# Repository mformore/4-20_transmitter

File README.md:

# 4-20mA and 0-10V Arduino Shield Transmitter

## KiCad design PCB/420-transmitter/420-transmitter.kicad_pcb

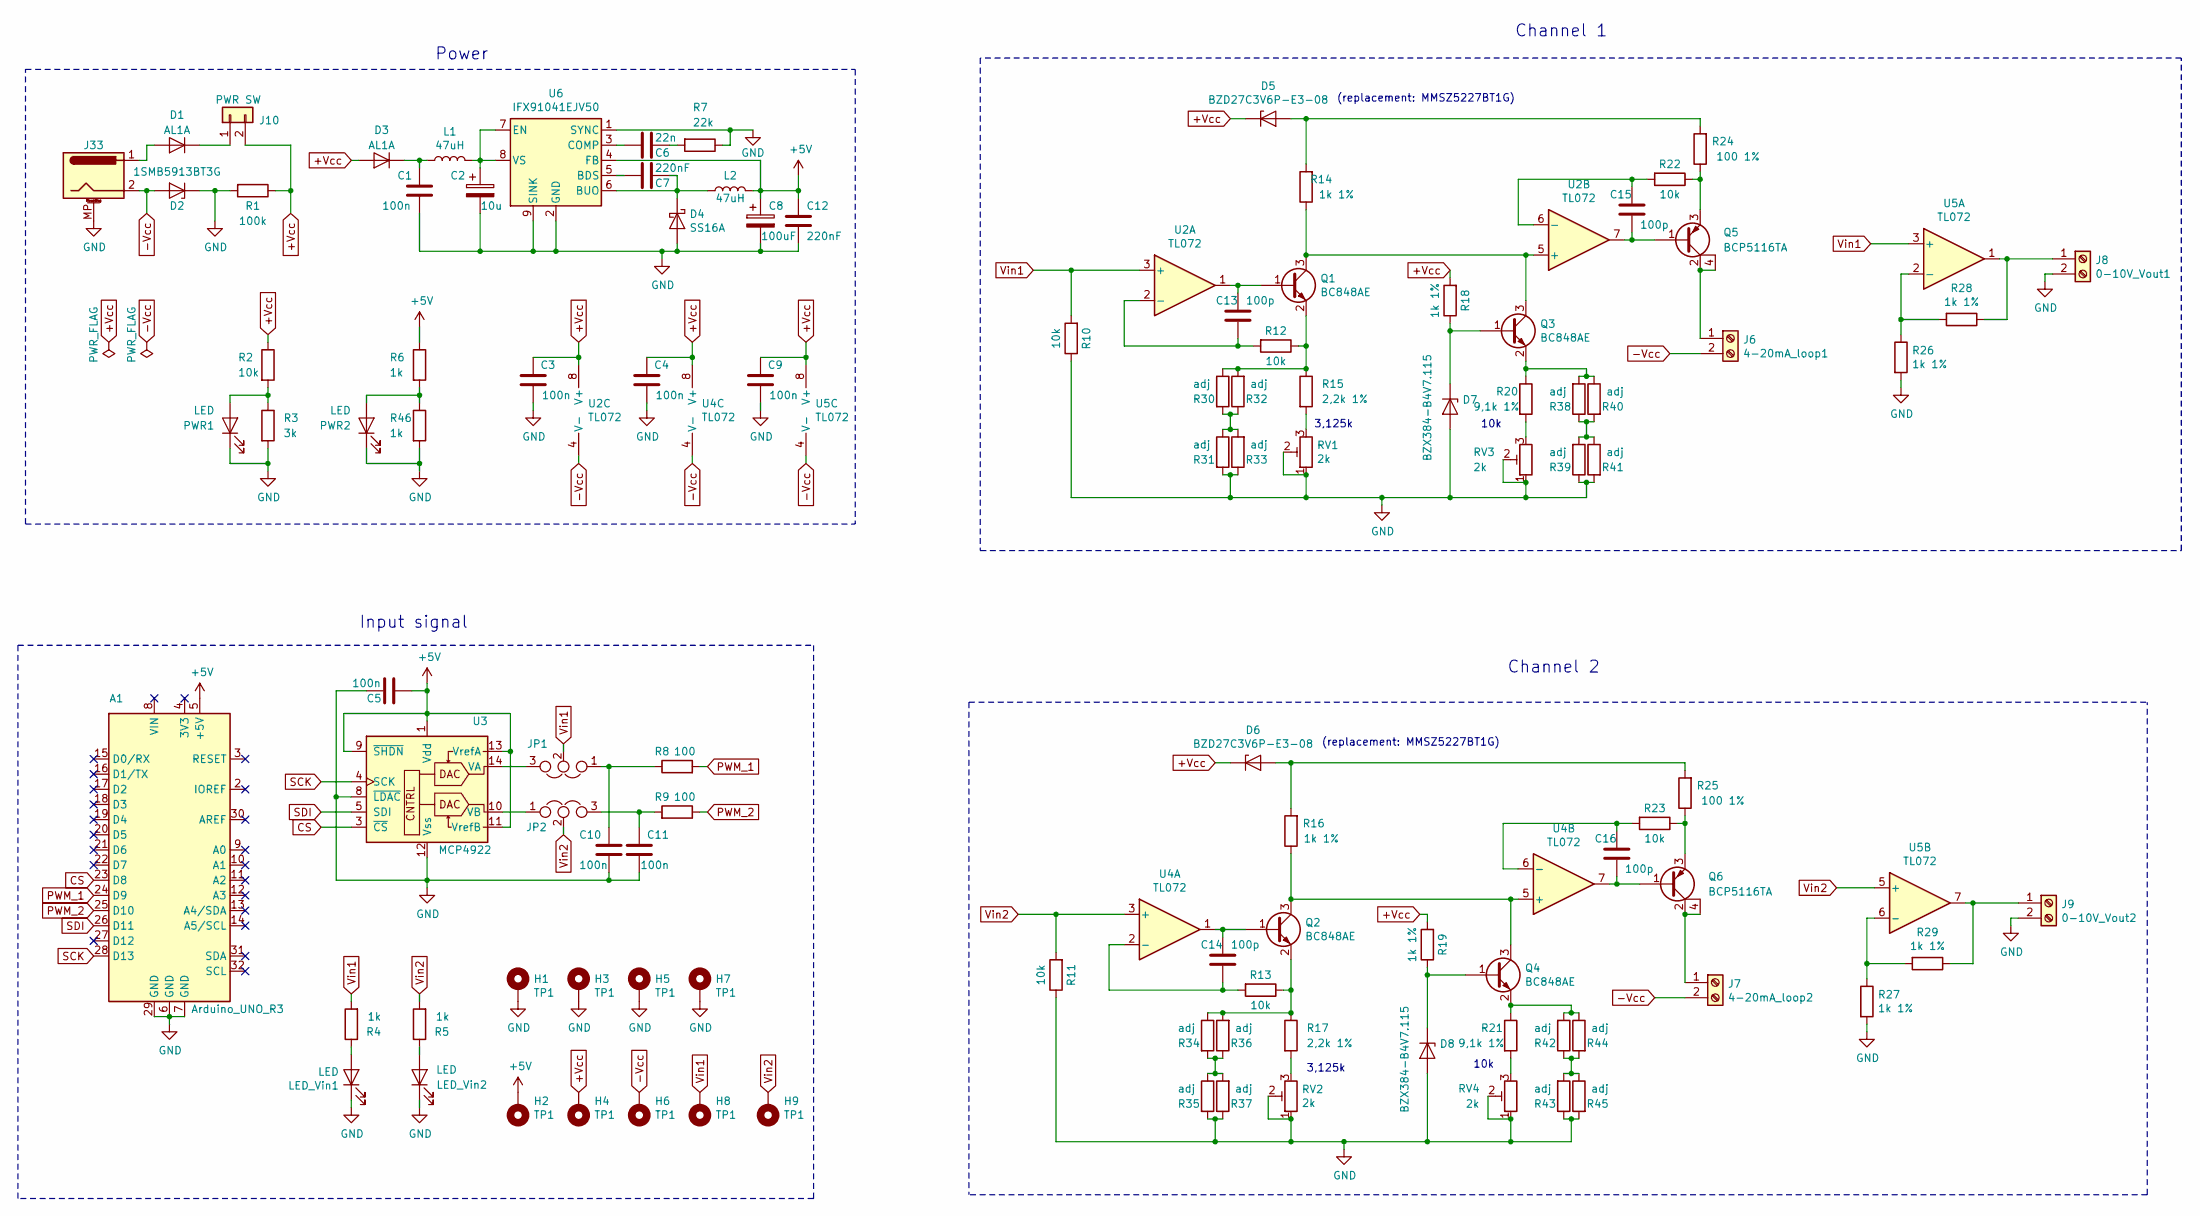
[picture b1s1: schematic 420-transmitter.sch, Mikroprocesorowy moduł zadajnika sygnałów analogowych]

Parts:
A1: Arduino_UNO_R3
C1, C3, C4, C5, C9, C10, C11: 100n; C_0805_2012Metric
C2: 10u; CP_Elec_6.3x5.3
C6: 22n; C_0805_2012Metric
C7, C12: 220nF; C_0805_2012Metric
C8: 100uF; CP_Elec_6.3x5.3
C13, C14, C15, C16: 100p; C_0805_2012Metric
D1, D3: AL1A; D_MiniMELF
D2: 1SMB5913BT3G; D_SMB
D4: SS16A; D_SMA
D5, D6: BZD27C3V6P-E3-08; D_SOD-123
D7, D8: BZX384-B4V7.115; D_SOD-323
H1, H2, H3, H4, H5, H6, H7, H8, H9: TP1; TestPoint_THTPad_D1.0mm_Drill0.5mm
J6: 4-20mA_loop1; TerminalBlock_bornier-2_P5.08mm
J7: 4-20mA_loop2; TerminalBlock_bornier-2_P5.08mm
J8: 0-10V_Vout1; TerminalBlock_bornier-2_P5.08mm
J9: 0-10V_Vout2; TerminalBlock_bornier-2_P5.08mm
J10: PWR SW; PinHeader_1x02_P2.54mm_Vertical
J33: Barrel_Jack_MountingPin; BarrelJack_Wuerth_6941xx301002
JP1: Vin1; PinHeader_1x03_P2.54mm_Vertical
JP2: Vin2; PinHeader_1x03_P2.54mm_Vertical
L1, L2: 47uH; L_Taiyo-Yuden_MD-5050
LED_Vin1, LED_Vin2: LED; LED_0805_2012Metric
PWR1, PWR2: LED; LED_0805_2012Metric
Q1, Q2, Q3, Q4: BC848AE; SOT-23
Q5, Q6: BCP5116TA; SOT-223
R1: 100k; R_1206_3216Metric
R2, R10, R11, R12, R13, R22, R23: 10k; R_0805_2012Metric
R3: 3k; R_0805_2012Metric
R4, R5, R6, R46: 1k; R_0805_2012Metric
R7: 22k; R_0805_2012Metric
R8, R9: 100; R_0805_2012Metric
R14, R16, R18, R19, R26, R27, R28, R29: 1k 1%; R_0805_2012Metric
R15, R17: 2,2k 1%; R_0805_2012Metric
R20, R21: 9,1k 1%; R_0805_2012Metric
R24, R25: 100 1%; R_2010_5025Metric
R30, R31, R32, R33, R34, R35, R36, R37, R38, R39, R40, R41, R42, R43, R44, R45: adj; R_0805_2012Metric
RV1, RV2, RV3, RV4: 2k; Potentiometer_Bourns_3296W_Vertical
U2, U4, U5: TL072; SO-8_5.3x6.2mm_P1.27mm
U3: MCP4922; SO14
U6: IFX91041EJV50; Infineon_PG-DSO-8-43

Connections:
+5V: A1.5 (+5V), C5.1, C8.1, C12.2, H2.1, L2.2, R6.1, U3.1 (Vdd), U3.9 (~SHDN), U3.11 (VrefB), U3.13 (VrefA), U6.4 (FB)
+Vcc: C3.1, C4.1, C9.1, D3.2 (A), D5.1 (K), D6.1 (K), H4.1, J10.2, R1.1, R2.1, R18.2, R19.2, U2.8 (V+), U4.8 (V+), U5.8 (V+)
-Vcc: D2.2 (A), H6.1, J6.2, J7.2, J33.2, U2.4 (V-), U4.4 (V-), U5.4 (V-)
CS: A1.23 (D8), U3.3 (~CS)
GND: A1.6 (GND), A1.7 (GND), A1.29 (GND), C1.2, C2.2, C3.2, C4.2, C5.2, C8.2, C9.2, C10.1, C11.1, C12.1, D2.1 (K), D4.2 (A), D7.2 (A), D8.2 (A), H1.1, H3.1, H5.1, H7.1, J8.2, J9.2, J33.MP (MountPin), LED_Vin1.1 (K), LED_Vin2.1 (K), PWR1.1 (K), PWR2.1 (K), R1.2, R3.2, R7.1, R10.1, R11.1, R26.2, R27.2, R31.2, R33.1, R35.2, R37.1, R39.1, R41.2, R43.1, R45.2, R46.2, RV1.1, RV1.2, RV2.1, RV2.2, RV3.1, RV3.2, RV4.1, RV4.2, U3.8 (~LDAC), U3.12 (Vss), U6.1 (SYNC), U6.2 (GND), U6.9 (SINK)
unnamed: C1.1, D3.1 (K), L1.1
unnamed: C2.1, L1.2, U6.7 (EN), U6.8 (VS)
unnamed: C6.1, R7.2
unnamed: C6.2, U6.3 (COMP)
unnamed: C7.1, U6.5 (BDS)
unnamed: C7.2, D4.1 (K), L2.1, U6.6 (BUO)
unnamed: C10.2, JP1.1, R8.1
unnamed: C11.2, JP2.3, R9.2
unnamed: C13.1, Q1.1 (B), U2.1
unnamed: C13.2, R12.2, U2.2 (-)
unnamed: C14.1, Q2.1 (B), U4.1
unnamed: C14.2, R13.2, U4.2 (-)
unnamed: C15.1, R22.2, U2.6 (-)
unnamed: C15.2, Q5.1 (B), U2.7
unnamed: C16.1, R23.2, U4.6 (-)
unnamed: C16.2, Q6.1 (B), U4.7
unnamed: D1.1 (K), J10.1
unnamed: D1.2 (A), J33.1
unnamed: D5.2 (A), R14.2, R24.2
unnamed: D6.2 (A), R16.2, R25.2
unnamed: D7.1 (K), Q3.1 (B), R18.1
unnamed: D8.1 (K), Q4.1 (B), R19.1
unnamed: J6.1, Q5.2 (C), Q5.4 (C)
unnamed: J7.1, Q6.2 (C), Q6.4 (C)
unnamed: J8.1, R28.1, U5.1
unnamed: J9.1, R29.1, U5.7
unnamed: JP1.3, U3.14 (VA)
unnamed: JP2.1, U3.10 (VB)
unnamed: LED_Vin1.2 (A), R4.1
unnamed: LED_Vin2.2 (A), R5.1
unnamed: PWR1.2 (A), R2.2, R3.1
unnamed: PWR2.2 (A), R6.2, R46.1
unnamed: Q1.2 (E), R12.1, R15.1, R30.1, R32.2
unnamed: Q1.3 (C), Q3.3 (C), R14.1, U2.5 (+)
unnamed: Q2.2 (E), R13.1, R17.1, R34.1, R36.2
unnamed: Q2.3 (C), Q4.3 (C), R16.1, U4.5 (+)
unnamed: Q3.2 (E), R20.1, R38.2, R40.1
unnamed: Q4.2 (E), R21.1, R42.2, R44.1
unnamed: Q5.3 (E), R22.1, R24.1
unnamed: Q6.3 (E), R23.1, R25.1
unnamed: R15.2, RV1.3
unnamed: R17.2, RV2.3
unnamed: R20.2, RV3.3
unnamed: R21.2, RV4.3
unnamed: R26.1, R28.2, U5.2 (-)
unnamed: R27.1, R29.2, U5.6 (-)
unnamed: R30.2, R31.1, R32.1, R33.2
unnamed: R34.2, R35.1, R36.1, R37.2
unnamed: R38.1, R39.2, R40.2, R41.1
unnamed: R42.1, R43.2, R44.2, R45.1
PWM_1: A1.24 (D9), R8.2
PWM_2: A1.25 (D10), R9.1
SCK: A1.28 (D13), U3.4 (SCK)
SDI: A1.26 (D11), U3.5 (SDI)
Vin1: H8.1, JP1.2, R4.2, R10.2, U2.3 (+), U5.3 (+)
Vin2: H9.1, JP2.2, R5.2, R11.2, U4.3 (+), U5.5 (+)

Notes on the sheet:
Power
Input signal
Channel 1
Channel 2
10k
3,125k
(replacement: MMSZ5227BT1G)

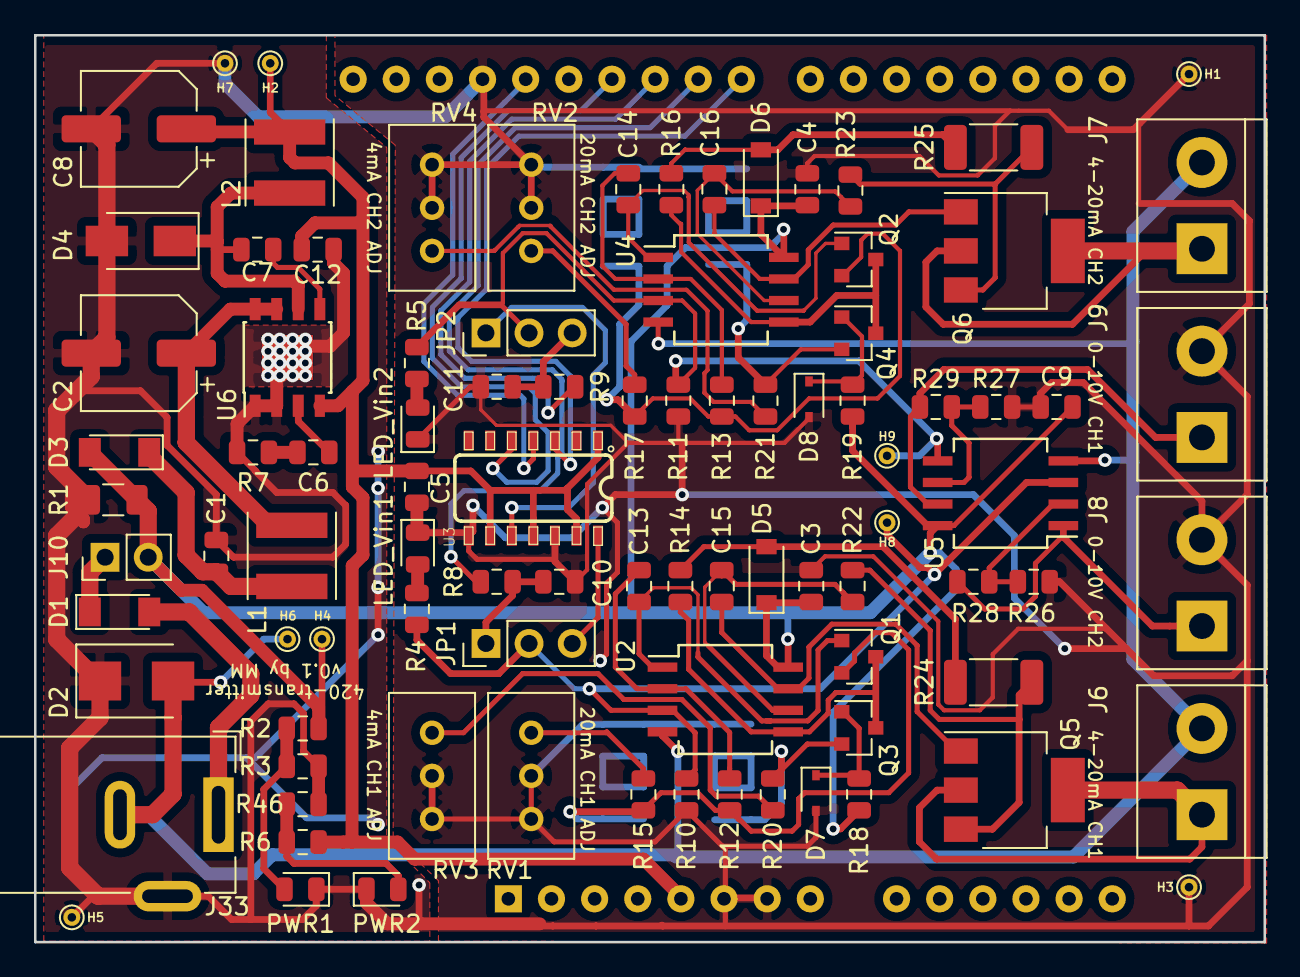
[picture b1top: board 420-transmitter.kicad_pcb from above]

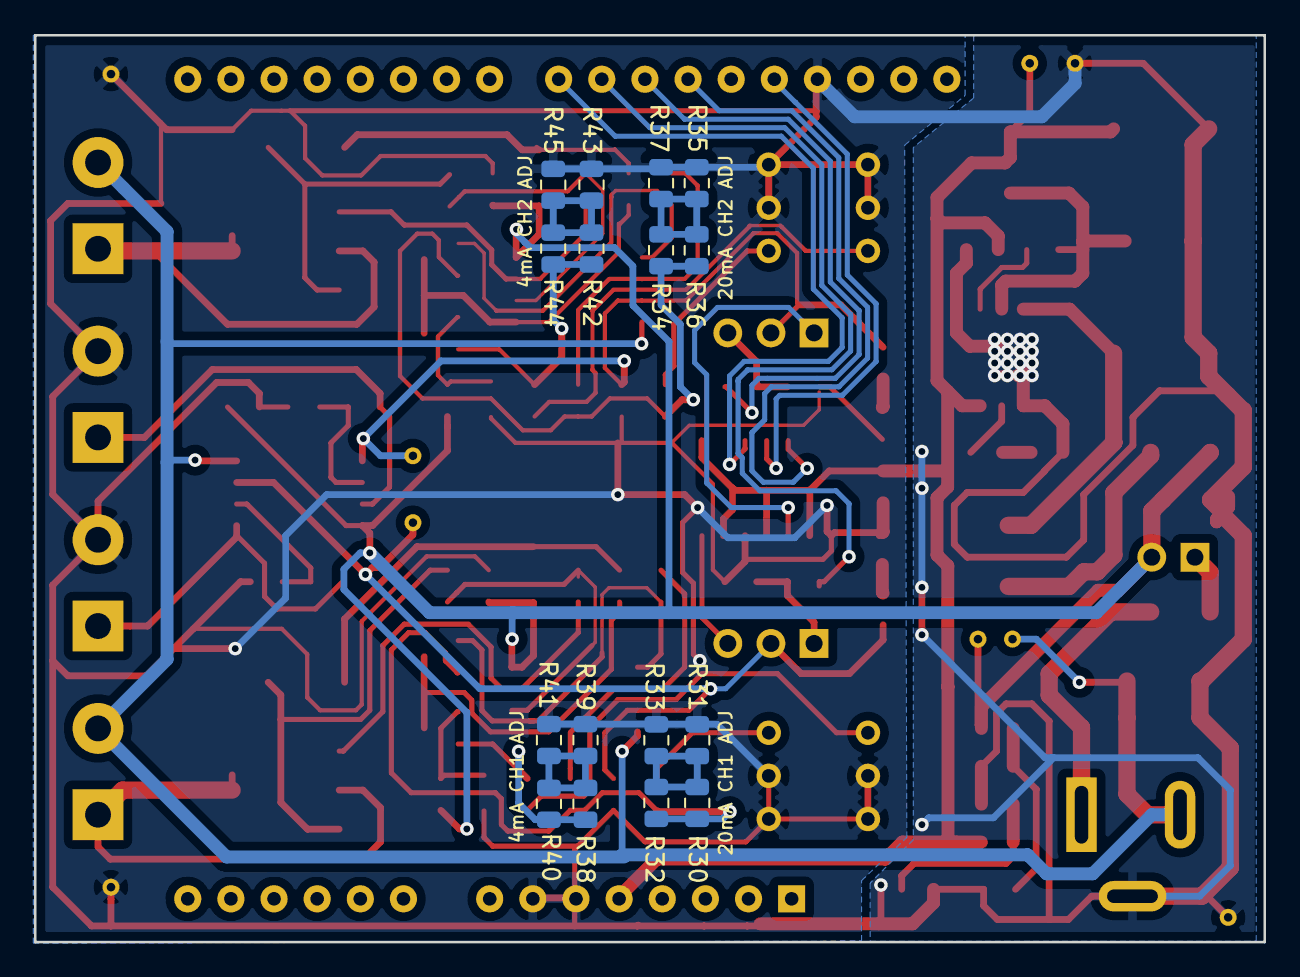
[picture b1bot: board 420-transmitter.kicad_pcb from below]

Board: 2 copper layers, 72.4 x 53.4 mm, 109 parts (17 on the bottom side), 61 nets.

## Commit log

2022-08-16 initial 420-transmitter reupload commit
2022-08-16 readme populated
